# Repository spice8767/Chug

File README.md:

# Chug
Chug is a small tabletop companion bot, capable of moving, expressing emotions via its eyes, and producing sound effects.
I would be using a Seeed Studio Xioa ESP32S3 Sense as the brain of the bot. The bot would use 2 N20 motors with Encoders for its movement.
A 128×96 SSD1327 1.32-inch OLED display would show the animated eyes of the bot, allowing it to express emotions like happiness, anger, etc.
An 8-ohm speaker, along with an Adafruit MAX98357A I2S 3W Class D Amplifier, is used to give the bot a mouth.
An MPU6050 is also included to allow the bot to detect when it is pushed around or picked from the ground, allowing for more emotive responses.

#Progress:
1. CAD - Done
2. PCB - Done
3. Parts Finalisation - Done
4. Ordering Parts - Pending
5. Code for Mobility of Bot - Working ON
6. Setting Up server and connection between the bot and the laptop - Pending
7. Display Code - Pending
8. Reaction Mechanisms - Pending
9. Code for Camera - Pending

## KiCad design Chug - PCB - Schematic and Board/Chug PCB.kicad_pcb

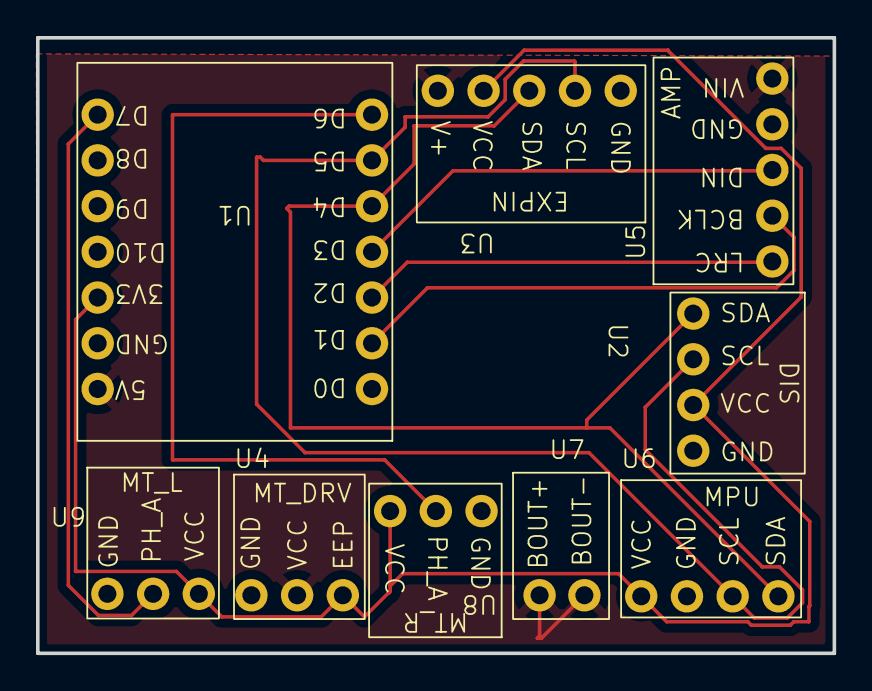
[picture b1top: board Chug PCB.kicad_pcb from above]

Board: 2 copper layers, 44.3 x 34.2 mm, 9 parts (0 on the bottom side), 10 nets.

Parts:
U1: ESP32S3
U2: OLED_Display
U3: Extension
U4: Motor_Driver
U5: Amplifier
U6: MPU6050
U7: Booster
U8: Motor_R
U9: Motor_L

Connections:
+3.3V: U1.11 (3V3), U2.3 (VCC), U3.17 (VCC), U4.12 (EEP), U6.1 (VCC), U8.5 (VCC), U9.5 (VCC)
+5V: U1.13 (5V), U3.16 (V+), U4.4 (VCC), U5.5 (VIN), U7.1 (OUT+)
GND: U1.12 (GND), U2.4 (GND), U3.20 (GND), U4.3 (GND), U5.4 (GND), U6.2 (GND), U8.2 (GND), U9.2 (GND)
unnamed: U1.1 (D1), U5.2 (BCLK)
unnamed: U1.2 (D2), U5.1 (LRC)
unnamed: U1.3 (D3), U5.3 (DIN)
unnamed: U1.4 (D4), U2.1 (SDA), U3.18 (SDA), U6.4 (SDA)
unnamed: U1.5 (D5), U2.2 (SCL), U3.19 (SCL), U6.3 (SCL)
unnamed: U1.6 (D6), U8.4 (C2)
unnamed: U1.7 (D7), U9.4 (C2)

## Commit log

2025-12-11 Create Body And Model
2025-12-15 Create IMAGES
